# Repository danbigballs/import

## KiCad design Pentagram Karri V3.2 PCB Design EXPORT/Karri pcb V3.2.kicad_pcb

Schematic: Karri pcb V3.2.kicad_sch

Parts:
5V_1: SOLDERJUMPERREFLOW_NOPASTE; SolderWirePad_1x01_SMD_1x2mm
BAT_IN_1: JST 2-PH; JST_PH_B2B-PH-SM4-TB_1x02-1MP_P2.00mm_Vertical
C1, C2, C3, C4, C8: 10uF; C_0603_1608Metric
C5: 100n
C9, C10: 220pF; C_0603_1608Metric
C11: 0.1uF; C_0603_1608Metric
C12: 10uF; C_0805_2012Metric
C13: 0.1uF; C_0805_2012Metric
C14: 2.2uF; Resistor_0805
C15: 100uF; C_1210_3225Metric
C16, C17: 10uF; Resistor_0805
C18: 1uF
C19: 220pF
CHN_DOWN1: SW_Push_Dual; TS-KG87S
CHN_UP1: SW_Push_Dual; TS-KG87S
CHRG/LBO1: ORANGE; LED_0805
D1, D2, D3, D4, D5, D6, D7, D8, D9, D10, D11, D12, D13, D14, D15, D16, D17, D18, D19, D20, D21, D22, D23, D24, D25, D26, D27, D28, D29, D30, D31, D32, D33, D34, D35, D36, D37, D38, D39, D40, D41, D42, D43, D44, D45, D46, D47, D48, D49, D50, D51, D52, D53, D54, D55, D56, D57, D58, D59, D60, D61, D62, D63, D73, D74, D75, D76, D77, D78, D79, D80, D81, D82, D83, D84, D85, D86, D87, D88, D89, D90, D91, D92, D93, D94, D95, D96, D97, D98, D99, D100, D101, D102, D103, D104, D105, D106, D107, D108, D109, D110, D111, D112, D113, D114, D115, D116, D117, D118, D119, D120, D121, D122, D123, D124, D125, D126, D127, D128, D129, D130, D131, D132, D133, D134, D135, D145, D146, D147, D148, D149, D150, D151, D152, D153, D154, D155, D156, D157, D158, D159, D160, D161, D162, D163, D164, D165, D166, D167, D168, D169, D170, D171, D172, D173, D174, D175, D176, D177, D178, D179, D180, D181, D182, D183, D184, D185, D186, D187, D188, D189, D190, D191, D192, D193, D194, D195, D196, D197, D198, D199, D200, D201, D202, D203, D204, D205, D206, D207, D217, D218, D219, D220, D221, D222, D223, D224, D225, D226, D227, D228, D229, D230, D231, D232, D233, D234, D235, D236, D237, D238, D239, D240, D241, D242, D243, D244, D245, D246, D247, D248, D249, D250, D251, D252, D253, D254, D255, D256, D257, D258, D259, D260, D261, D262, D263, D264, D265, D266, D267, D268, D269, D270: 0402 LED; LED_0402_1005Metric
D332, D333, D334: 1N4148; D_SOD-323
DONE1: GREEN; LED_0805
DOWN_U5: A3144; SOT-23
FB1, FB2: Resistor_0805
FID1, FID2, FID3: FIDUCIAL""; FIDUCIAL_1MM
GND_1: SOLDERJUMPERREFLOW_NOPASTE; SolderWirePad_1x01_SMD_1x2mm
H1, H2, H3, H4, H5, H6, H7: MountingHole; MountingHole_2.2mm_M2_DIN965_Pad
IC1: HT16K33 SSOP; SSOP-24_3.9x8.7mm_P0.635mm
IC2, IC3, IC4: HT16K33; SSOP-24_3.9x8.7mm_P0.635mm
J1: GPIO; PinSocket_2x20_P2.54mm_Vertical_SMD
J4: Power; JST_SH_SM02B-SRSS-TB_1x02-1MP_P1.00mm_Horizontal
J5: USB_IN; JST_SH_SM02B-SRSS-TB_1x02-1MP_P1.00mm_Horizontal
J6: USB_C_Receptacle_PowerOnly_6P; USB_C_Receptacle_GCT_USB4135-GF-A_6P_TopMnt_Horizontal
JP1: ID_WP
L1: 6.8uH; L_APV_ANR5045
LED1: RED; LED_0805
LED2: BLUE; LED_0805
LS1, LS2: Speaker; AS01506MS
MK1: ICS-43434; InvenSense_ICS-43434-6_3.5x2.65mm
OUT4: SOLDERJUMPERREFLOW_NOPASTE; SolderWirePad_1x01_SMD_1x2mm
R1, R2: 3.9k
R3, R4, R12, R13: 10K; Resistor_0402
R6: 1M?; Resistor_0402
R7, R20: 1.87M; Resistor_0805
R8, R9, R10, R11: 47K; R_0603_1608Metric
R14: 340K; Resistor_0805
R15, R21: 200K; Resistor_0805
R16: 10K; R_0805_2012Metric
R17: 47K; R_0805_2012Metric
R18: 68; R_0805_2012Metric
R22, R23: 1K; Resistor_0805
R24, R25: 1K; R_0805_2012Metric
R26: 270K; Resistor_0805
R27, R29: 100K; R_0805_2012Metric
R28: 1.0K; R_0805_2012Metric
SCL1: SOLDERJUMPERREFLOW_NOPASTE; SolderWirePad_1x01_SMD_1x2mm
SDA1: SOLDERJUMPERREFLOW_NOPASTE; SolderWirePad_1x01_SMD_1x2mm
SW2: KILL_SWITCH; XKB5858-Z-F-75
SW3: Wake; SW_SPDT_PCM12
T1: MMUN2133LT1G; SC-59
THERM1: 15K; Resistor_0805
U1: CAT24C256
U2: MAX98357A; TQFN-16-1EP_3x3mm_P0.5mm_EP1.23x1.23mm
U4: TPS61090RSAR; Texas_RSA_VQFN-16-1EP_4x4mm_P0.65mm_EP2.7x2.7mm_ThermalVias
U5: MCP73871; Texas_RGP0020H_VQFN-20-1EP_4x4mm_P0.5mm_EP2.4x2.4mm
U$1, U$2: MOUNTINGHOLE2.5; MOUNTINGHOLE_2.5_PLATED
UP_U4: A3144; SOT-23
VO+1: VO-; JST_SH_SM02B-SRSS-TB_1x02-1MP_P1.00mm_Horizontal
VOL+1: SOLDERJUMPERREFLOW_NOPASTE; SolderWirePad_1x01_SMD_1x2mm
VOL-1: SOLDERJUMPERREFLOW_NOPASTE; SolderWirePad_1x01_SMD_1x2mm
VOL_DOWN1: SW_Push_Dual; TS-KG87S
VOL_UP1: SW_Push_Dual; TS-KG87S

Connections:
+3V3: C5.1, C18.1, C19.1, J1.1, J1.17, JP1.2 (B), MK1.5 (VDD), R1.1, R2.1, U1.8 (VCC)
+5V: 5V_1.1, C1.2, C2.2, C3.2, C4.2, C8.1, C11.1, C14.1, C15.1, DOWN_U5.1 (VCC), IC1.24 (VDD), IC2.24 (VDD), IC3.24 (VDD), IC4.24 (VDD), J1.2, J1.4, J4.1, R3.1, R4.1, R6.1, R12.1, R13.1, R20.2, R23.1, U2.7 (VDD), U2.8 (VDD), U4.1 (VOUT), U4.15 (VOUT), U4.16 (VOUT), UP_U4.1 (VCC)
/ENABLE: R15.2, SW2.4, SW3.2, U4.11 (EN)
/GPIO2/SDA1: IC1.23 (SDA), IC2.23 (SDA), IC3.23 (SDA), IC4.23 (SDA), J1.3, R3.2, SDA1.1
/GPIO3/SCL1: IC1.22 (SCL), IC2.22 (SCL), IC3.22 (SCL), IC4.22 (SCL), J1.5, R4.2, SCL1.1
/GPIO4/GPCLK0: J1.7
/GPIO6: J1.31
/GPIO7/SPI0.CE1: DOWN_U5.2 (OUT), J1.26, R12.2
/GPIO8/SPI0.CE0: J1.24, R13.2, UP_U4.2 (OUT)
/GPIO9/SPI0.MISO: J1.21
/GPIO10/SPI0.MOSI: J1.19
/GPIO11/SPI0.SCLK: J1.23
/GPIO12/PWM0: J1.32
/GPIO13/PWM1: J1.33
/GPIO14/TXD0: J1.8
/GPIO15/RXD0: J1.10
/GPIO16: J1.36
/GPIO17: CHN_UP1.1, J1.11
/GPIO18/PCM.CLK: J1.12, MK1.4 (SCK), U2.16 (BCLK)
/GPIO19/PCM.FS: J1.35, MK1.1 (WS), U2.14 (LRCLK)
/GPIO20/PCM.DIN: J1.38, R18.2
/GPIO21/PCM.DOUT: J1.40, U2.1 (DIN)
/GPIO23: J1.16, VOL_UP1.1
/GPIO24: J1.18, VOL_DOWN1.1
/GPIO25: J1.22
/GPIO26: J1.37
/GPIO27: CHN_DOWN1.1, J1.13
/ID_SCL: J1.28, R2.2, U1.6 (SCL)
/ID_SDA: J1.27, R1.2, U1.5 (SDA)
/LBO: T1.1, U4.12 (LBO)
GND: BAT_IN_1.1 (-), C1.1, C2.1, C3.1, C4.1, C5.2, C8.2, C9.2, C10.2, C11.2, C12.2, C13.2, C14.2, C15.2, C16.2, C17.2, C18.2, C19.2, CHN_DOWN1.3, CHN_UP1.3, DOWN_U5.3 (GND), GND_1.1, IC1.1 (VSS), IC2.1 (VSS), IC3.1 (VSS), IC4.1 (VSS), J1.6, J1.9, J1.14, J1.20, J1.25, J1.30, J1.34, J1.39, J4.2, J5.1, J6.A12 (GND), J6.B12 (GND), LED1.1, LED2.2, MK1.3 (GND), R14.1, R16.2, R17.2, R21.1, R27.2, R28.1, R29.1, SW2.2, SW3.3, THERM1.1, U1.4 (GND), U2.3 (GND), U2.11 (GND), U2.15 (GND), U4.5 (PGND), U4.6 (PGND), U4.7 (PGND), U4.10 (SYNC), U4.13 (GND), U4.17, U4.P$18 (PGND), U4.P$19 (PGND), U4.P$20 (PGND), U4.P$21 (PGND), U4.P$22 (PGND), U4.THERMAL (PGND), U5.10 (VSS1), U5.11 (VSS2), U5.21 (THERMAL), UP_U4.3 (GND), VOL_DOWN1.3, VOL_UP1.3
unnamed: CHRG/LBO1.2 (C), R24.2
unnamed: D1.2 (A), D10.2 (A), D19.2 (A), D28.2 (A), D37.2 (A), D46.2 (A), D55.2 (A), IC1.21 (ROW0/A1)
unnamed: D1.1 (K), D2.1 (K), D3.1 (K), D4.1 (K), D5.1 (K), D6.1 (K), D7.1 (K), D8.1 (K), D9.1 (K), IC1.2 (COM0/AD)
unnamed: D10.1 (K), D11.1 (K), D12.1 (K), D13.1 (K), D14.1 (K), D15.1 (K), D16.1 (K), D17.1 (K), D18.1 (K), IC1.3 (COM1/KS0)
unnamed: D2.2 (A), D11.2 (A), D20.2 (A), D29.2 (A), D38.2 (A), D47.2 (A), D56.2 (A), IC1.20 (ROW1/A0)
unnamed: D3.2 (A), D12.2 (A), D21.2 (A), D30.2 (A), D39.2 (A), D48.2 (A), D57.2 (A), IC1.19 (ROW2/K1)
unnamed: D4.2 (A), D13.2 (A), D22.2 (A), D31.2 (A), D40.2 (A), D49.2 (A), D58.2 (A), IC1.18 (ROW3/K2)
unnamed: D5.2 (A), D14.2 (A), D23.2 (A), D32.2 (A), D41.2 (A), D50.2 (A), D59.2 (A), IC1.17 (ROW4/K3)
unnamed: D6.2 (A), D15.2 (A), D24.2 (A), D33.2 (A), D42.2 (A), D51.2 (A), D60.2 (A), IC1.16 (ROW5/K4)
unnamed: D7.2 (A), D16.2 (A), D25.2 (A), D34.2 (A), D43.2 (A), D52.2 (A), D61.2 (A), IC1.15 (ROW6/K5)
unnamed: D8.2 (A), D17.2 (A), D26.2 (A), D35.2 (A), D44.2 (A), D53.2 (A), D62.2 (A), IC1.14 (ROW7/K6)
unnamed: D9.2 (A), D18.2 (A), D27.2 (A), D36.2 (A), D45.2 (A), D54.2 (A), D63.2 (A), IC1.13 (ROW8/K7)
unnamed: D19.1 (K), D20.1 (K), D21.1 (K), D22.1 (K), D23.1 (K), D24.1 (K), D25.1 (K), D26.1 (K), D27.1 (K), IC1.4 (COM2/KS1)
unnamed: D28.1 (K), D29.1 (K), D30.1 (K), D31.1 (K), D32.1 (K), D33.1 (K), D34.1 (K), D35.1 (K), D36.1 (K), IC1.5 (COM3/KS2)
unnamed: D37.1 (K), D38.1 (K), D39.1 (K), D40.1 (K), D41.1 (K), D42.1 (K), D43.1 (K), D44.1 (K), D45.1 (K), IC1.6 (COM4)
unnamed: D46.1 (K), D47.1 (K), D48.1 (K), D49.1 (K), D50.1 (K), D51.1 (K), D52.1 (K), D53.1 (K), D54.1 (K), IC1.7 (COM5)
unnamed: D55.1 (K), D56.1 (K), D57.1 (K), D58.1 (K), D59.1 (K), D60.1 (K), D61.1 (K), D62.1 (K), D63.1 (K), IC1.8 (COM6)
unnamed: D82.1 (K), D83.1 (K), D84.1 (K), D85.1 (K), D86.1 (K), D87.1 (K), D88.1 (K), D89.1 (K), D90.1 (K), IC2.3 (COM1/KS0)
unnamed: D91.1 (K), D92.1 (K), D93.1 (K), D94.1 (K), D95.1 (K), D96.1 (K), D97.1 (K), D98.1 (K), D99.1 (K), IC2.4 (COM2/KS1)
unnamed: D73.2 (A), D82.2 (A), D91.2 (A), D100.2 (A), D109.2 (A), D118.2 (A), D127.2 (A), IC2.21 (ROW0/A1)
unnamed: D100.1 (K), D101.1 (K), D102.1 (K), D103.1 (K), D104.1 (K), D105.1 (K), D106.1 (K), D107.1 (K), D108.1 (K), IC2.5 (COM3/KS2)
unnamed: D74.2 (A), D83.2 (A), D92.2 (A), D101.2 (A), D110.2 (A), D119.2 (A), D128.2 (A), IC2.20 (ROW1/A0), R8.2
unnamed: D75.2 (A), D84.2 (A), D93.2 (A), D102.2 (A), D111.2 (A), D120.2 (A), D129.2 (A), IC2.19 (ROW2/K1)
unnamed: D76.2 (A), D85.2 (A), D94.2 (A), D103.2 (A), D112.2 (A), D121.2 (A), D130.2 (A), IC2.18 (ROW3/K2)
unnamed: D77.2 (A), D86.2 (A), D95.2 (A), D104.2 (A), D113.2 (A), D122.2 (A), D131.2 (A), IC2.17 (ROW4/K3)
unnamed: D78.2 (A), D87.2 (A), D96.2 (A), D105.2 (A), D114.2 (A), D123.2 (A), D132.2 (A), IC2.16 (ROW5/K4)
unnamed: D79.2 (A), D88.2 (A), D97.2 (A), D106.2 (A), D115.2 (A), D124.2 (A), D133.2 (A), IC2.15 (ROW6/K5)
unnamed: D80.2 (A), D89.2 (A), D98.2 (A), D107.2 (A), D116.2 (A), D125.2 (A), D134.2 (A), IC2.14 (ROW7/K6)
unnamed: D81.2 (A), D90.2 (A), D99.2 (A), D108.2 (A), D117.2 (A), D126.2 (A), D135.2 (A), IC2.13 (ROW8/K7)
unnamed: D109.1 (K), D110.1 (K), D111.1 (K), D112.1 (K), D113.1 (K), D114.1 (K), D115.1 (K), D116.1 (K), D117.1 (K), IC2.6 (COM4)
unnamed: D118.1 (K), D119.1 (K), D120.1 (K), D121.1 (K), D122.1 (K), D123.1 (K), D124.1 (K), D125.1 (K), D126.1 (K), IC2.7 (COM5)
unnamed: D127.1 (K), D128.1 (K), D129.1 (K), D130.1 (K), D131.1 (K), D132.1 (K), D133.1 (K), D134.1 (K), D135.1 (K), IC2.8 (COM6)
unnamed: D145.2 (A), D154.2 (A), D163.2 (A), D172.2 (A), D181.2 (A), D190.2 (A), D199.2 (A), IC3.21 (ROW0/A1), R9.2
unnamed: D145.1 (K), D146.1 (K), D147.1 (K), D148.1 (K), D149.1 (K), D150.1 (K), D151.1 (K), D152.1 (K), D153.1 (K), D333.2 (A), IC3.2 (COM0/AD)
unnamed: D146.2 (A), D155.2 (A), D164.2 (A), D173.2 (A), D182.2 (A), D191.2 (A), D200.2 (A), IC3.20 (ROW1/A0)
unnamed: D147.2 (A), D156.2 (A), D165.2 (A), D174.2 (A), D183.2 (A), D192.2 (A), D201.2 (A), IC3.19 (ROW2/K1)
unnamed: D148.2 (A), D157.2 (A), D166.2 (A), D175.2 (A), D184.2 (A), D193.2 (A), D202.2 (A), IC3.18 (ROW3/K2)
unnamed: D149.2 (A), D158.2 (A), D167.2 (A), D176.2 (A), D185.2 (A), D194.2 (A), D203.2 (A), IC3.17 (ROW4/K3)
unnamed: D150.2 (A), D159.2 (A), D168.2 (A), D177.2 (A), D186.2 (A), D195.2 (A), D204.2 (A), IC3.16 (ROW5/K4)
unnamed: D151.2 (A), D160.2 (A), D169.2 (A), D178.2 (A), D187.2 (A), D196.2 (A), D205.2 (A), IC3.15 (ROW6/K5)
unnamed: D152.2 (A), D161.2 (A), D170.2 (A), D179.2 (A), D188.2 (A), D197.2 (A), D206.2 (A), IC3.14 (ROW7/K6)
unnamed: D153.2 (A), D162.2 (A), D171.2 (A), D180.2 (A), D189.2 (A), D198.2 (A), D207.2 (A), IC3.13 (ROW8/K7)
unnamed: D154.1 (K), D155.1 (K), D156.1 (K), D157.1 (K), D158.1 (K), D159.1 (K), D160.1 (K), D161.1 (K), D162.1 (K), IC3.3 (COM1/KS0)
unnamed: D163.1 (K), D164.1 (K), D165.1 (K), D166.1 (K), D167.1 (K), D168.1 (K), D169.1 (K), D170.1 (K), D171.1 (K), IC3.4 (COM2/KS1)
unnamed: D172.1 (K), D173.1 (K), D174.1 (K), D175.1 (K), D176.1 (K), D177.1 (K), D178.1 (K), D179.1 (K), D180.1 (K), IC3.5 (COM3/KS2)
unnamed: D181.1 (K), D182.1 (K), D183.1 (K), D184.1 (K), D185.1 (K), D186.1 (K), D187.1 (K), D188.1 (K), D189.1 (K), IC3.6 (COM4)
unnamed: D190.1 (K), D191.1 (K), D192.1 (K), D193.1 (K), D194.1 (K), D195.1 (K), D196.1 (K), D197.1 (K), D198.1 (K), IC3.7 (COM5)
unnamed: D199.1 (K), D200.1 (K), D201.1 (K), D202.1 (K), D203.1 (K), D204.1 (K), D205.1 (K), D206.1 (K), D207.1 (K), IC3.8 (COM6)
unnamed: D217.2 (A), D226.2 (A), D235.2 (A), D244.2 (A), D253.2 (A), D262.2 (A), IC4.21 (ROW0/A1), R10.2
unnamed: D217.1 (K), D218.1 (K), D219.1 (K), D220.1 (K), D221.1 (K), D222.1 (K), D223.1 (K), D224.1 (K), D225.1 (K), D334.2 (A), IC4.2 (COM0/AD)
unnamed: D218.2 (A), D227.2 (A), D236.2 (A), D245.2 (A), D254.2 (A), D263.2 (A), IC4.20 (ROW1/A0), R11.2
unnamed: D219.2 (A), D228.2 (A), D237.2 (A), D246.2 (A), D255.2 (A), D264.2 (A), IC4.19 (ROW2/K1)
unnamed: D220.2 (A), D229.2 (A), D238.2 (A), D247.2 (A), D256.2 (A), D265.2 (A), IC4.18 (ROW3/K2)
unnamed: D221.2 (A), D230.2 (A), D239.2 (A), D248.2 (A), D257.2 (A), D266.2 (A), IC4.17 (ROW4/K3)
unnamed: D222.2 (A), D231.2 (A), D240.2 (A), D249.2 (A), D258.2 (A), D267.2 (A), IC4.16 (ROW5/K4)
unnamed: D223.2 (A), D232.2 (A), D241.2 (A), D250.2 (A), D259.2 (A), D268.2 (A), IC4.15 (ROW6/K5)
unnamed: D224.2 (A), D233.2 (A), D242.2 (A), D251.2 (A), D260.2 (A), D269.2 (A), IC4.14 (ROW7/K6)
unnamed: D225.2 (A), D234.2 (A), D243.2 (A), D252.2 (A), D261.2 (A), D270.2 (A), IC4.13 (ROW8/K7)
unnamed: D226.1 (K), D227.1 (K), D228.1 (K), D229.1 (K), D230.1 (K), D231.1 (K), D232.1 (K), D233.1 (K), D234.1 (K), IC4.3 (COM1/KS0)
unnamed: D235.1 (K), D236.1 (K), D237.1 (K), D238.1 (K), D239.1 (K), D240.1 (K), D241.1 (K), D242.1 (K), D243.1 (K), IC4.4 (COM2/KS1)
unnamed: D244.1 (K), D245.1 (K), D246.1 (K), D247.1 (K), D248.1 (K), D249.1 (K), D250.1 (K), D251.1 (K), D252.1 (K), IC4.5 (COM3/KS2)
unnamed: D253.1 (K), D254.1 (K), D255.1 (K), D256.1 (K), D257.1 (K), D258.1 (K), D259.1 (K), D260.1 (K), D261.1 (K), IC4.6 (COM4)
unnamed: D262.1 (K), D263.1 (K), D264.1 (K), D265.1 (K), D266.1 (K), D267.1 (K), D268.1 (K), D269.1 (K), D270.1 (K), IC4.7 (COM5)
unnamed: D73.1 (K), D74.1 (K), D75.1 (K), D76.1 (K), D77.1 (K), D78.1 (K), D79.1 (K), D80.1 (K), D81.1 (K), D332.2 (A), IC2.2 (COM0/AD)
unnamed: D332.1 (K), R8.1
unnamed: D333.1 (K), R9.1
unnamed: D334.1 (K), R10.1, R11.1
unnamed: DONE1.2 (C), R25.2
unnamed: FB1.1, U2.9 (OUTP)
unnamed: C10.1, FB1.2, LS1.1, VO+1.1, VOL+1.1
unnamed: FB2.1, U2.10 (OUTN)
unnamed: C9.1, FB2.2, LS2.2, VO+1.2, VOL-1.1
unnamed: JP1.1 (A), U1.7 (WP)
unnamed: L1.2, U4.3 (SW), U4.4 (SW)
unnamed: LED1.2, R22.1
unnamed: LED2.1, R23.2
unnamed: LS1.2, LS2.1
unnamed: MK1.2 (LR), R16.1
unnamed: MK1.6 (SD), OUT4.1, R17.1, R18.1
unnamed: R22.2, T1.3
unnamed: R6.2, U2.4 (~SD_MODE)
unnamed: R20.1, R21.2, U4.14 (FB)
unnamed: R7.1, R14.2, U4.9 (LBI)
unnamed: R28.2, U5.13 (PROG1)
unnamed: R29.2, U5.12 (PROG3)
unnamed: R24.1, U5.8 (STAT1/LBO)
unnamed: R25.1, U5.7 (STAT2)
unnamed: THERM1.2, U5.5 (THERM)
unnamed: R26.1, R27.1, U5.2 (VPCC)
VBAT: C12.1, C13.1, L1.1, R7.2, R15.1, T1.2, U4.8 (VBAT), U5.1 (VOUT1), U5.20 (VOUT2)
VBUS: C16.1, CHRG/LBO1.1 (A), DONE1.1 (A), J5.2, J6.A9 (VBUS), J6.B9 (VBUS), R26.2, U5.3 (SEL), U5.4 (PROG2), U5.9 (/TE), U5.17 (CE), U5.18 (VIN1), U5.19 (VIN2)
VLIPO: BAT_IN_1.2 (+), C17.1, SW3.1, U5.14 (VBAT1), U5.15 (VBAT2), U5.16 (VBATSENS)

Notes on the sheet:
5V OUT
Both grounds must be connected on the PCB at only one point close to the GND pin.
1.0K = 1000mA
No Thermistor:
RT1 = 0, RT2 = 10K
10K NTC Thermistor:
RT1 = TBD, RT2 = TBD
See Pg 15 1st para
6.8uH power w/2A current
ID_SD and ID_SC PINS: These pins are reserved for HAT ID EEPROM. At boot time this I2C interface will be interrogated to look for an EEPROM that identifes the attached board and allows automagic setup of the GPIOs (and optionally, Linux drivers). Bridging JP1 enables write protection. DO NOT USE th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
2.0K = 500mA
R3 = 1.9Mohm for 5.2V R3 = 1.1Mohm for 3.3V
ICS-43434
Digital hall sensors
MAX983587
On/Off Switch
Charge Rate = 1000V/PROG1
Additional pin functions: https://pinout.xyz/

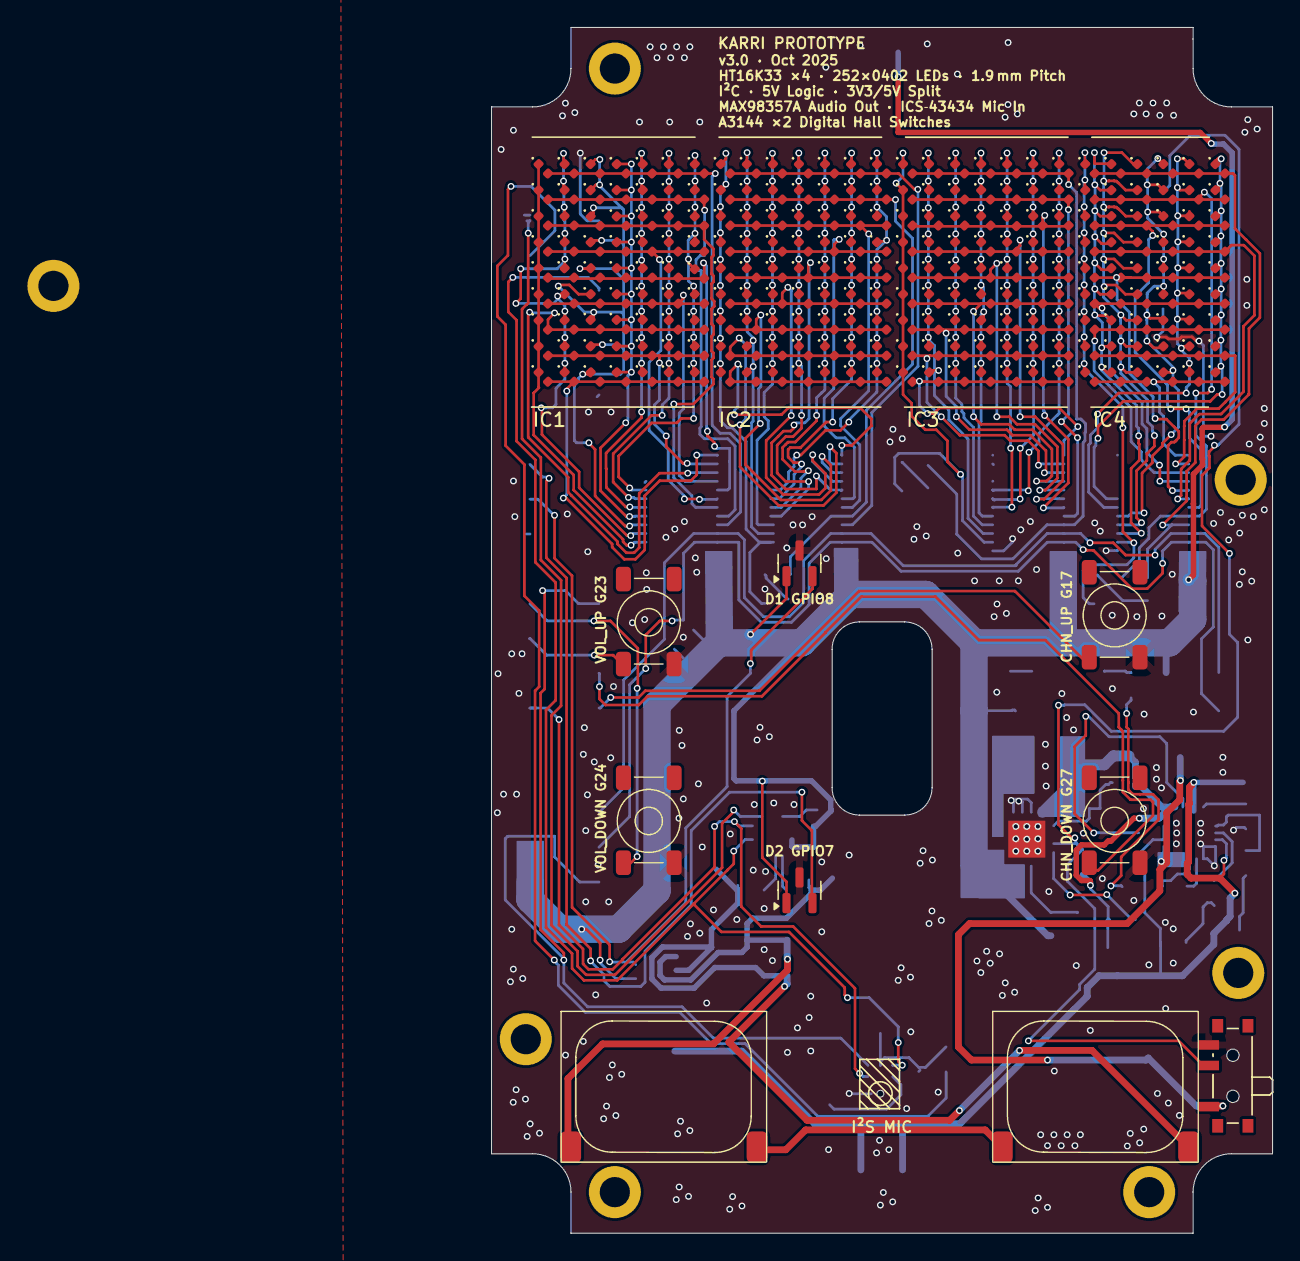
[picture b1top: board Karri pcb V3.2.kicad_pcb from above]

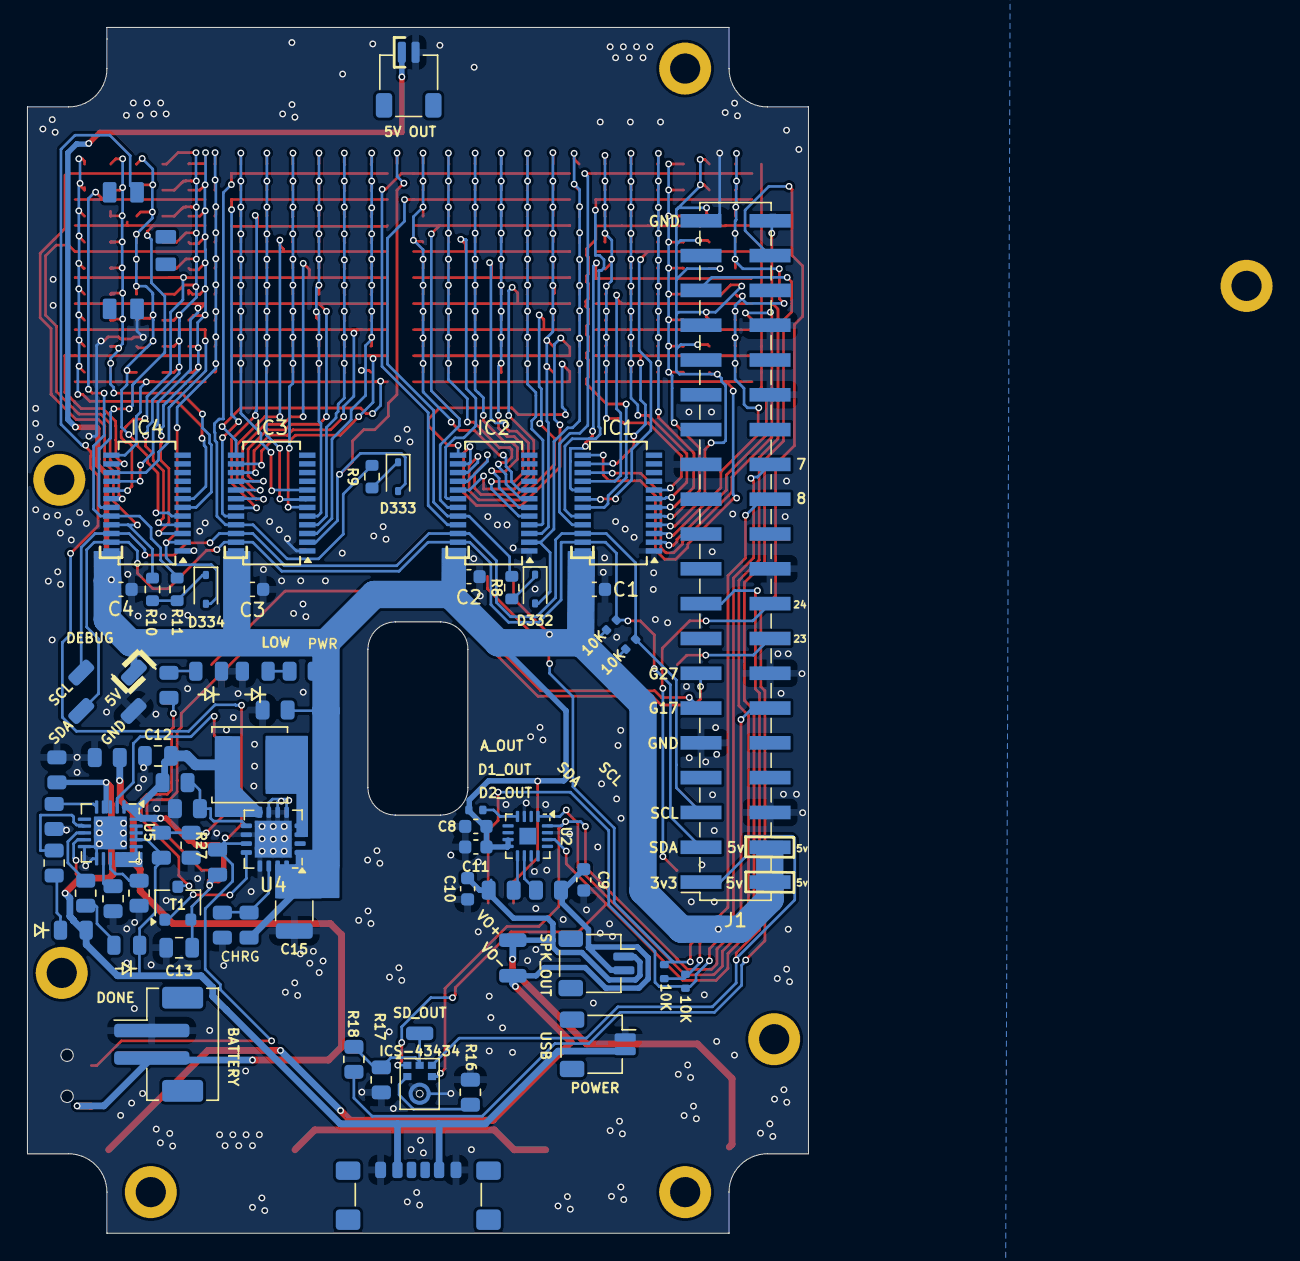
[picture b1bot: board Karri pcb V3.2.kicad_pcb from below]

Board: 2 copper layers, 57.0 x 88.0 mm, 332 parts (74 on the bottom side), 108 nets.

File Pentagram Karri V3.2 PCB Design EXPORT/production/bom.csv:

Designator,Footprint,Quantity,Value,LCSC Part #
"5V_1, GND_1, OUT4, SCL1, SDA1, VOL+1, VOL-1",SolderWirePad_1x01_SMD_1x2mm,7,SOLDERJUMPERREFLOW_NOPASTE,
BAT_IN_1,JST_PH_B2B-PH-SM4-TB_1x02-1MP_P2.00mm_Vertical,1,JST 2-PH,
"C1, C2, C3, C4, C8",0603,5,10uF,
"C10, C9",0603,2,220pF,
C11,0603,1,0.1uF,
C12,0805,1,10uF,
C13,0805,1,0.1uF,
C14,Resistor_0805,1,2.2uF,
C15,1210,1,100uF,
"C16, C17",Resistor_0805,2,10uF,
"CHN_DOWN1, CHN_UP1, VOL_DOWN1, VOL_UP1",TS-KG87S,4,SW_Push_Dual,
CHRG/LBO1,LED_0805,1,ORANGE,
"D1, D10, D100, D101, D102, D103, D104, D105, D106, D107, D108, D109, D11, D110, D111, D112, D113, D114, D115, D116, D117, D118, D119, D12, D120, D121, D122, D123, D124, D125, D126, D127, D128, D129, D13, D130, D131, D132, D133, D134, D135, D14, D145, D146, D147, D148, D149, D15, D150, D151, D152, D153, D154, D155, D156, D157, D158, D159, D16, D160, D161, D162, D163, D164, D165, D166, D167, D168, D169, D17, D170, D171, D172, D173, D174, D175, D176, D177, D178, D179, D18, D180, D181, D182, D183, D184, D185, D186, D187, D188, D189, D19, D190, D191, D192, D193, D194, D195, D196, D197, D198, D199, D2, D20, D200, D201, D202, D203, D204, D205, D206, D207, D21, D217, D218, D219, D22, D220, D221, D222, D223, D224, D225, D226, D227, D228, D229, D23, D230, D231, D232, D233, D234, D235, D236, D237, D238, D239, D24, D240, D241, D242, D243, D244, D245, D246, D247, D248, D249, D25, D250, D251, D252, D253, D254, D255, D256, D257, D258, D259, D26, D260, D261, D262, D263, D264, D265, D266, D267, D268, D269, D27, D270, D28, D29, D3, D30, D31, D32, D33, D34, D35, D36, D37, D38, D39, D4, D40, D41, D42, D43, D44, D45, D46, D47, D48, D49, D5, D50, D51",0402,200,0402 LED,
"D332, D333, D334",D_SOD-323,3,1N4148,
"D52, D53, D54, D55, D56, D57, D58, D59, D6, D60, D61, D62, D63, D7, D73, D74, D75, D76, D77, D78, D79, D8, D80, D81, D82, D83, D84, D85, D86, D87, D88, D89, D9, D90, D91, D92, D93, D94, D95, D96, D97, D98, D99",0402,43,0402 LED,
DONE1,LED_0805,1,GREEN,
"DOWN_U5, UP_U4",SOT-23,2,A3144,
"FB1, FB2",Resistor_0805,2,~,
IC1,SSOP-24_3.9x8.7mm_P0.635mm,1,HT16K33 SSOP,
"IC2, IC3, IC4",SSOP-24_3.9x8.7mm_P0.635mm,3,HT16K33,
J1,PinSocket_2x20_P2.54mm_Vertical_SMD,1,GPIO,
J4,JST_SH_SM02B-SRSS-TB_1x02-1MP_P1.00mm_Horizontal,1,Power,
J5,JST_SH_SM02B-SRSS-TB_1x02-1MP_P1.00mm_Horizontal,1,USB_IN,
J6,USB_C_Receptacle_GCT_USB4135-GF-A_6P_TopMnt_Horizontal,1,USB_C_Receptacle_PowerOnly_6P,
L1,L_APV_ANR5045,1,6.8uH,
LED1,LED_0805,1,RED,
LED2,LED_0805,1,BLUE,
"LS1, LS2",AS01506MS,2,Speaker,
MK1,InvenSense_ICS-43434-6_3.5x2.65mm,1,ICS-43434,
"R10, R11, R8, R9",0603,4,47K,
"R12, R13, R3, R4",Resistor_0402,4,10K,
R14,Resistor_0805,1,340K,
"R15, R21",Resistor_0805,2,200K,
R16,0805,1,10K,
R17,0805,1,47K,
R18,0805,1,68,
"R20, R7",Resistor_0805,2,1.87M,
"R22, R23",Resistor_0805,2,1K,
"R24, R25",0805,2,1K,
R26,Resistor_0805,1,270K,
"R27, R29",0805,2,100K,
R28,0805,1,1.0K,
R6,Resistor_0402,1,1M?,
SW2,XKB5858-Z-F-75,1,KILL_SWITCH,
SW3,SW_SPDT_PCM12,1,Wake,
T1,SC-59,1,MMUN2133LT1G,
THERM1,Resistor_0805,1,15K,
U2,TQFN-16-1EP_3x3mm_P0.5mm_EP1.23x1.23mm,1,MAX98357A,
U4,Texas_RSA_VQFN-16-1EP_4x4mm_P0.65mm_EP2.7x2.7mm_ThermalVias,1,TPS61090RSAR,
U5,Texas_RGP0020H_VQFN-20-1EP_4x4mm_P0.5mm_EP2.4x2.4mm,1,MCP73871,
VO+1,JST_SH_SM02B-SRSS-TB_1x02-1MP_P1.00mm_Horizontal,1,VO-,

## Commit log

2026-03-28 Karri pcb design upload
2026-03-28 ORBIT PCB DESIGN1V!
2026-03-28 Karri python codes for raspberry pi
